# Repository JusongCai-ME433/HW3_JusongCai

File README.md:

# HW3_JusongCai

In this homework, you can see Gerbers in the zip file. The Gerbers are the PCB I completed and errors are checked. The zip file "HW3_Gerbers_JusongCai" will be uploaded and used to order the designed board. Also, updated Eagle files can be found in this repo in "ME433_2018" folder.

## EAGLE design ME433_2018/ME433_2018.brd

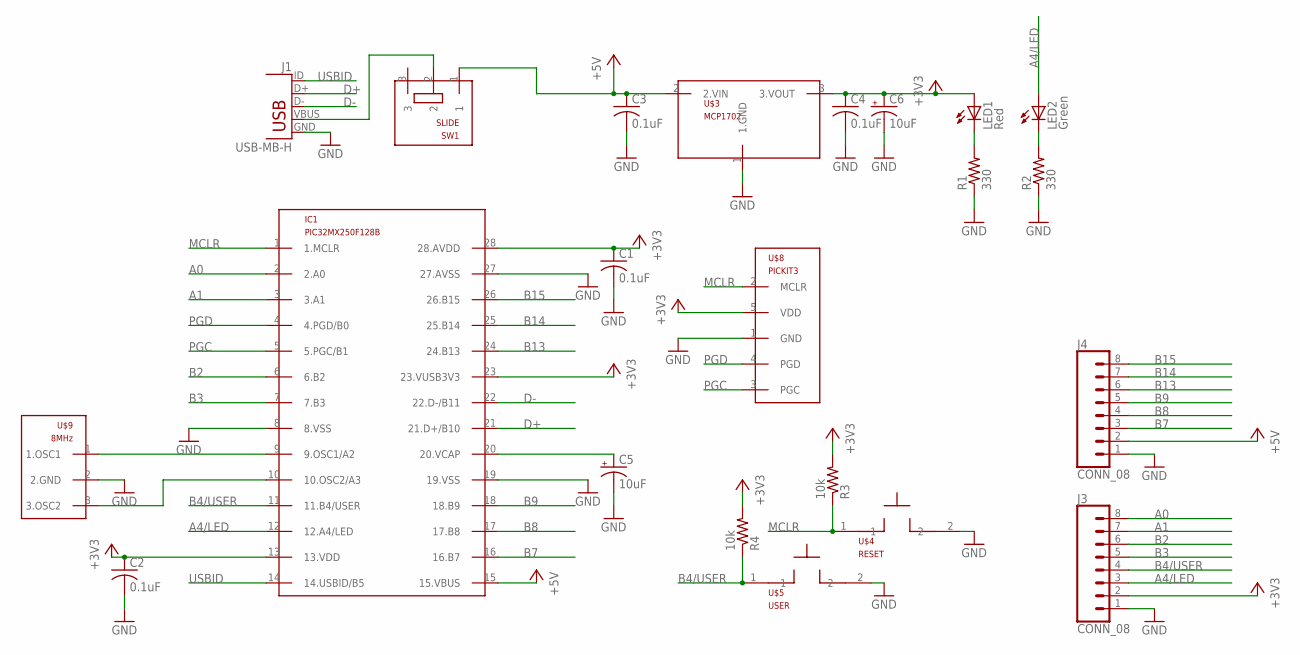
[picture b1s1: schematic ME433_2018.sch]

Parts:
C1, C2, C3, C4: 0.1uF; C025-025X050
C5, C6: 10uF; B45181B
IC1: PIC32MX250F128B; DIL28-3
J1: USB-MB-H
J3, J4: CONN_08; 1X08
LED1: Red; LED3MM
LED2: Green; LED3MM
R1, R2: 330; 0207/10
R3, R4: 10k; 0207/10
SW1: SLIDE
U$3: MCP1702; TO92
U$4: RESET; PB
U$5: USER; PB
U$8: PICKIT3; 1X05
U$9: 8MHz; OSC

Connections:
+3V3: C1.1, C2.1, C4.1, C6.+, IC1.13 (13.VDD), IC1.23 (23.VUSB3V3), IC1.28 (28.AVDD), J3.2, LED1.A, R3.2, R4.2, U$3.3 (3.VOUT), U$8.5 (VDD)
+5V: C3.1, IC1.15 (15.VBUS), J4.2, SW1.1, U$3.2 (2.VIN)
A0: IC1.2 (2.A0), J3.8
A1: IC1.3 (3.A1), J3.7
A4/LED: IC1.12 (12.A4/LED), J3.3, LED2.A
B2: IC1.6 (6.B2), J3.6
B3: IC1.7 (7.B3), J3.5
B4/USER: IC1.11 (11.B4/USER), J3.4, R4.1, U$5.1
B7: IC1.16 (16.B7), J4.3
B8: IC1.17 (17.B8), J4.4
B9: IC1.18 (18.B9), J4.5
B13: IC1.24 (24.B13), J4.6
B14: IC1.25 (25.B14), J4.7
B15: IC1.26 (26.B15), J4.8
D+: IC1.21 (21.D+/B10), J1.D+
D-: IC1.22 (22.D-/B11), J1.D-
GND: C1.2, C2.2, C3.2, C4.2, C5.-, C6.-, IC1.8 (8.VSS), IC1.19 (19.VSS), IC1.27 (27.AVSS), J1.GND, J3.1, J4.1, R1.1, R2.1, U$3.1 (1.GND), U$4.2, U$5.2, U$8.1 (GND), U$9.2 (2.GND)
MCLR: IC1.1 (1.MCLR), R3.1, U$4.1, U$8.2 (MCLR)
unnamed: J1.VBUS, SW1.2
unnamed: LED2.K (C), R2.2
unnamed: LED1.K (C), R1.2
unnamed: IC1.9 (9.OSC1/A2), U$9.1 (1.OSC1)
unnamed: IC1.10 (10.OSC2/A3), U$9.3 (3.OSC2)
unnamed: C5.+, IC1.20 (20.VCAP)
PGC: IC1.5 (5.PGC/B1), U$8.3 (PGC)
PGD: IC1.4 (4.PGD/B0), U$8.4 (PGD)
USBID: IC1.14 (14.USBID/B5), J1.ID

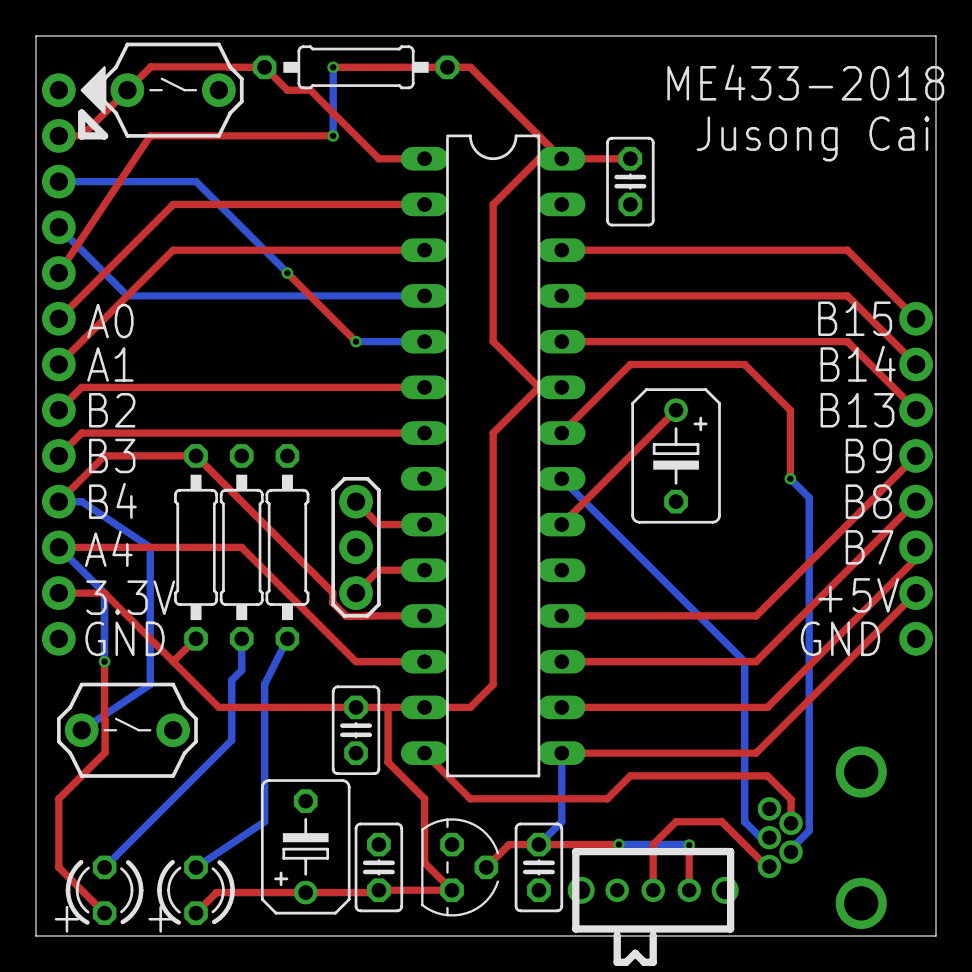
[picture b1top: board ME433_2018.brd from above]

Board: 2 copper layers, 50.0 x 50.0 mm, 22 parts (0 on the bottom side), 27 nets.

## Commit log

2018-04-17 upload Gerbers zip and update Eagle files
